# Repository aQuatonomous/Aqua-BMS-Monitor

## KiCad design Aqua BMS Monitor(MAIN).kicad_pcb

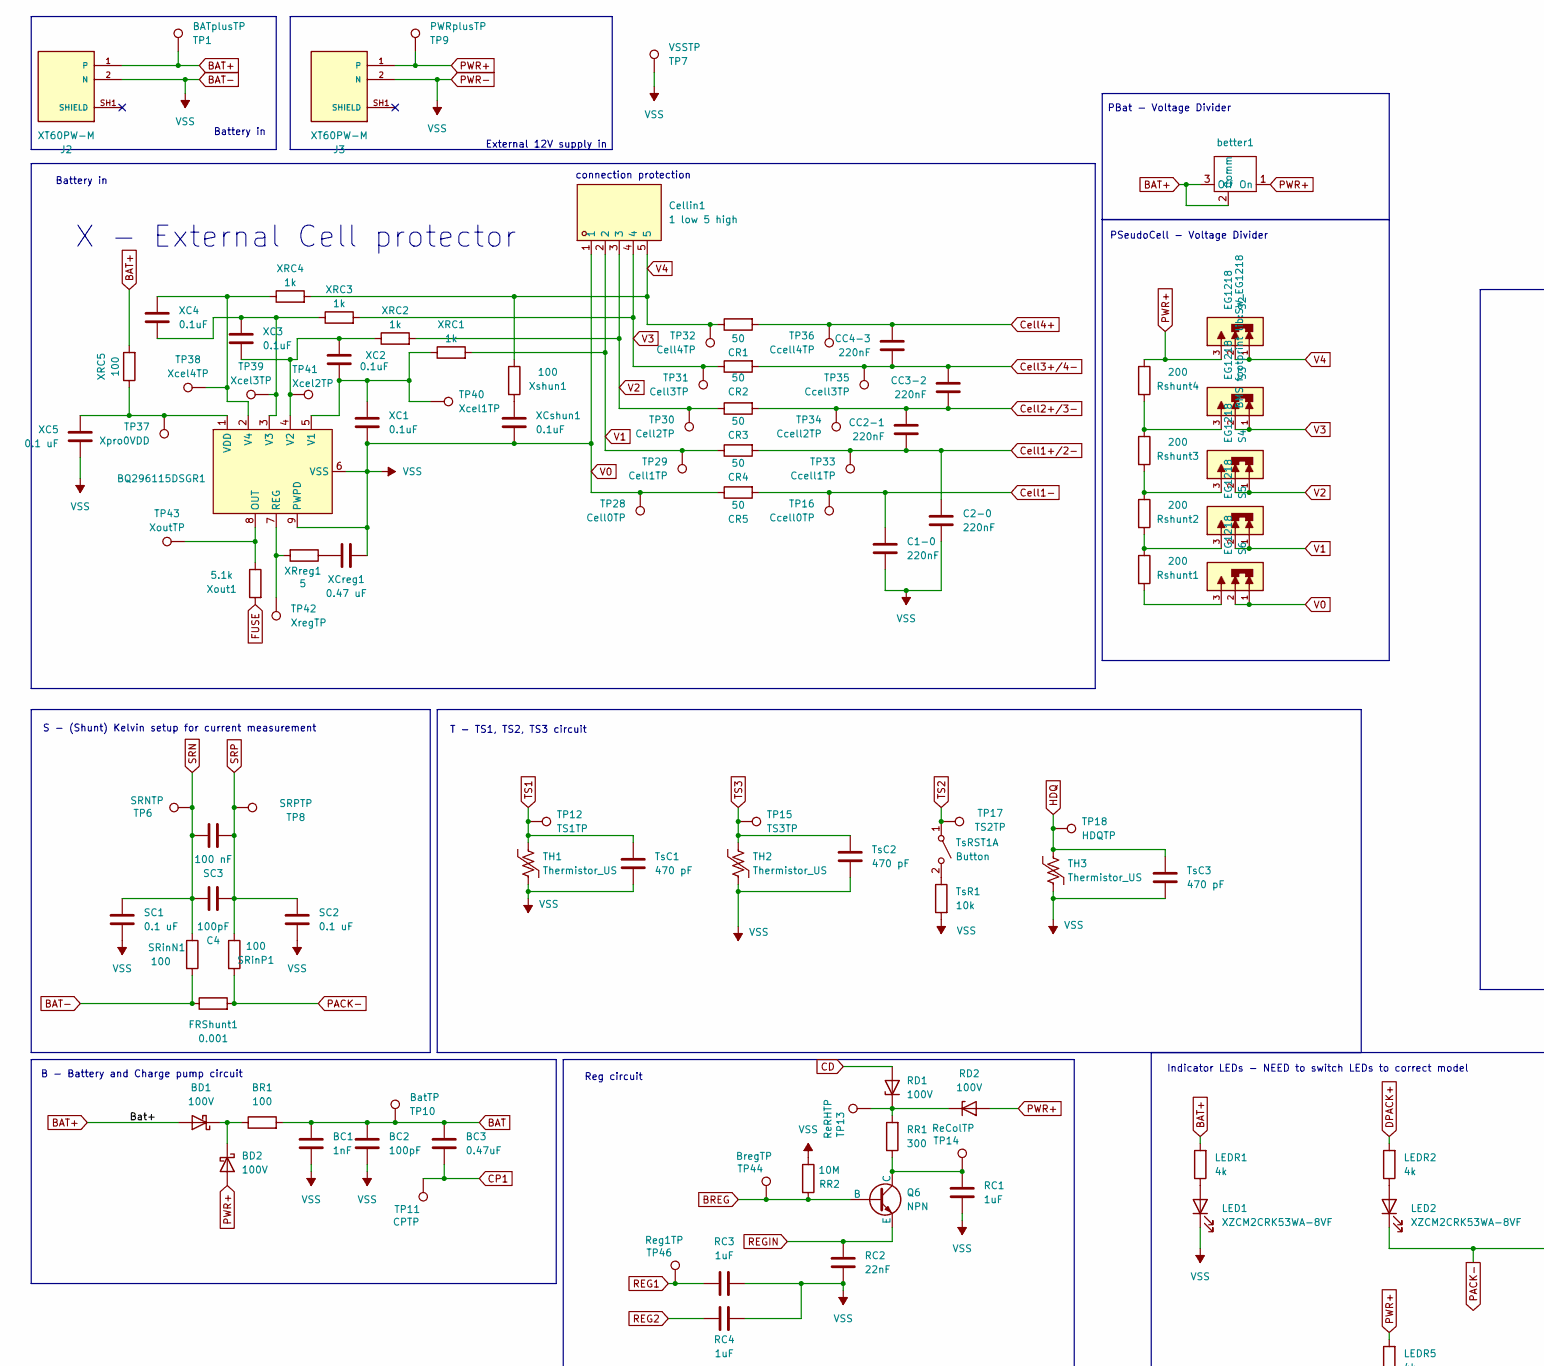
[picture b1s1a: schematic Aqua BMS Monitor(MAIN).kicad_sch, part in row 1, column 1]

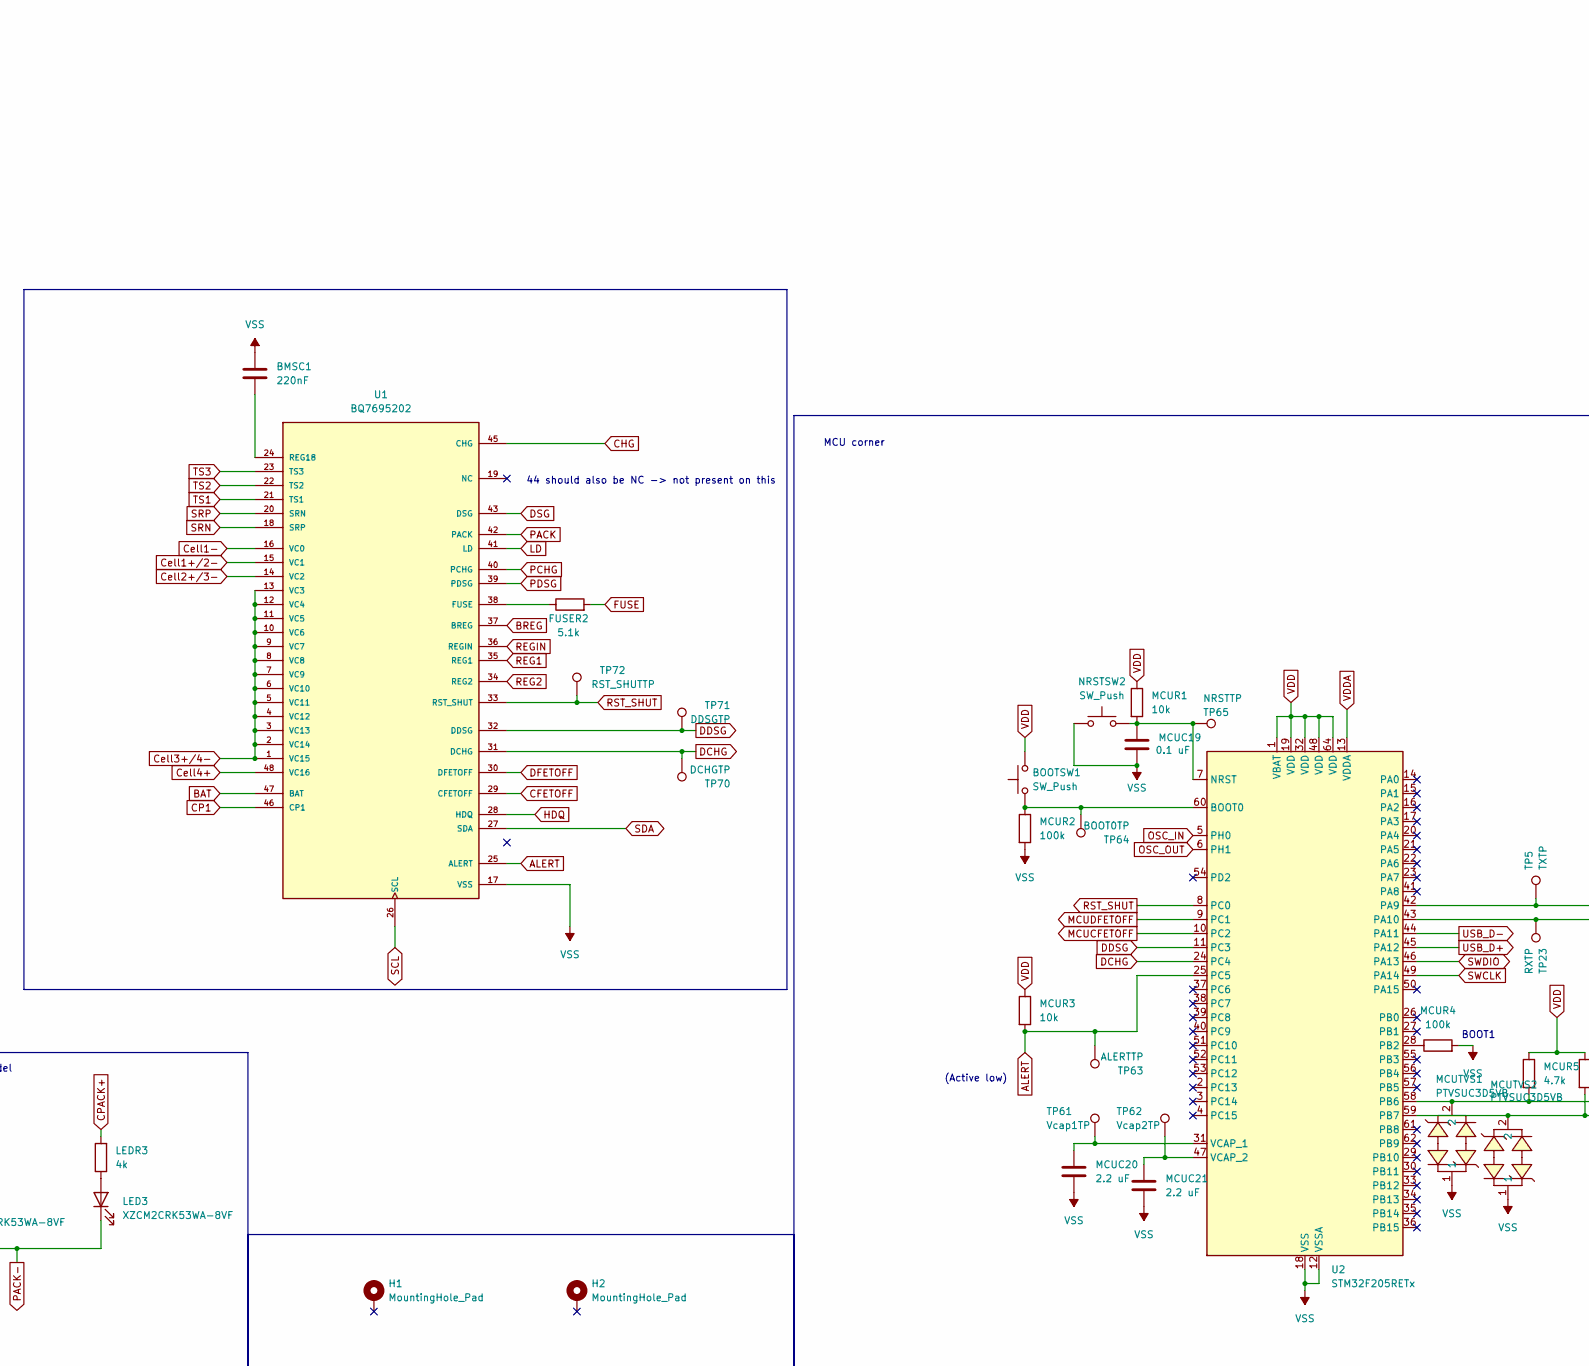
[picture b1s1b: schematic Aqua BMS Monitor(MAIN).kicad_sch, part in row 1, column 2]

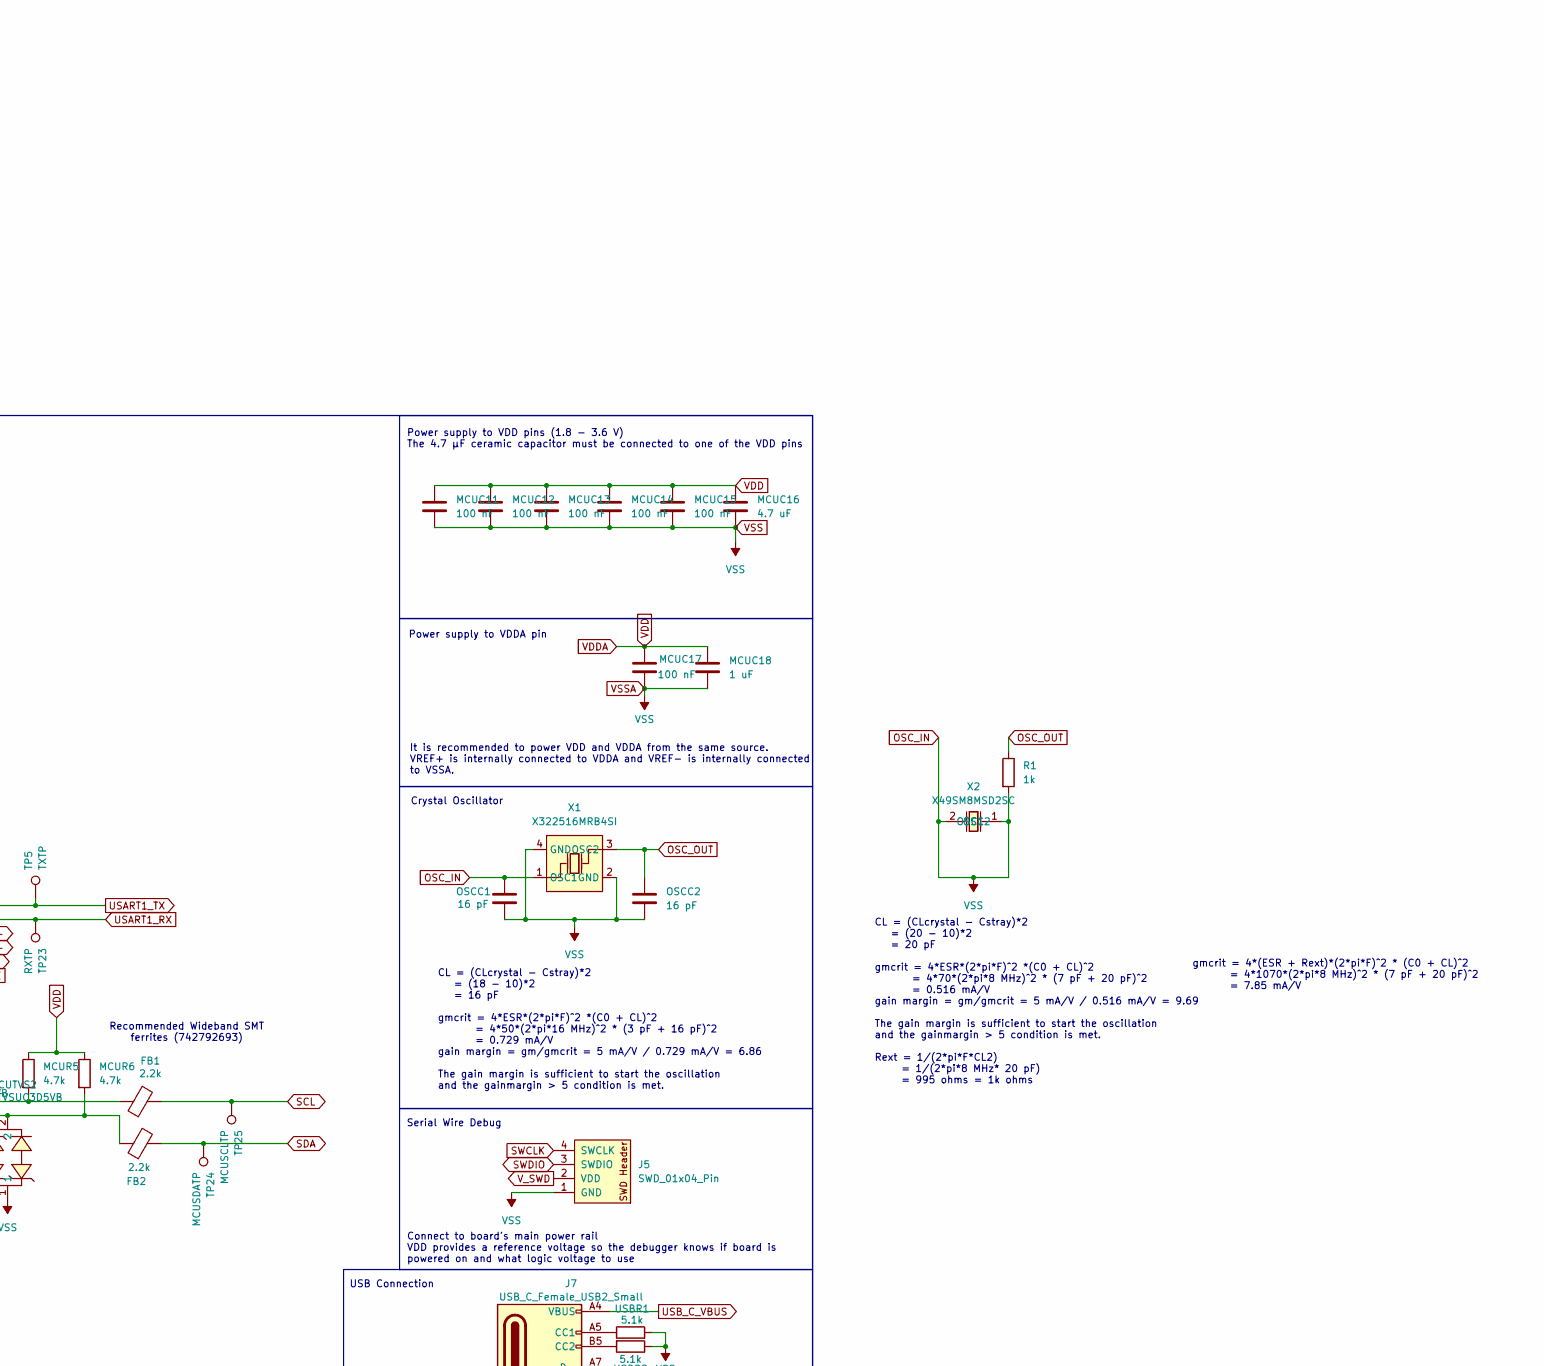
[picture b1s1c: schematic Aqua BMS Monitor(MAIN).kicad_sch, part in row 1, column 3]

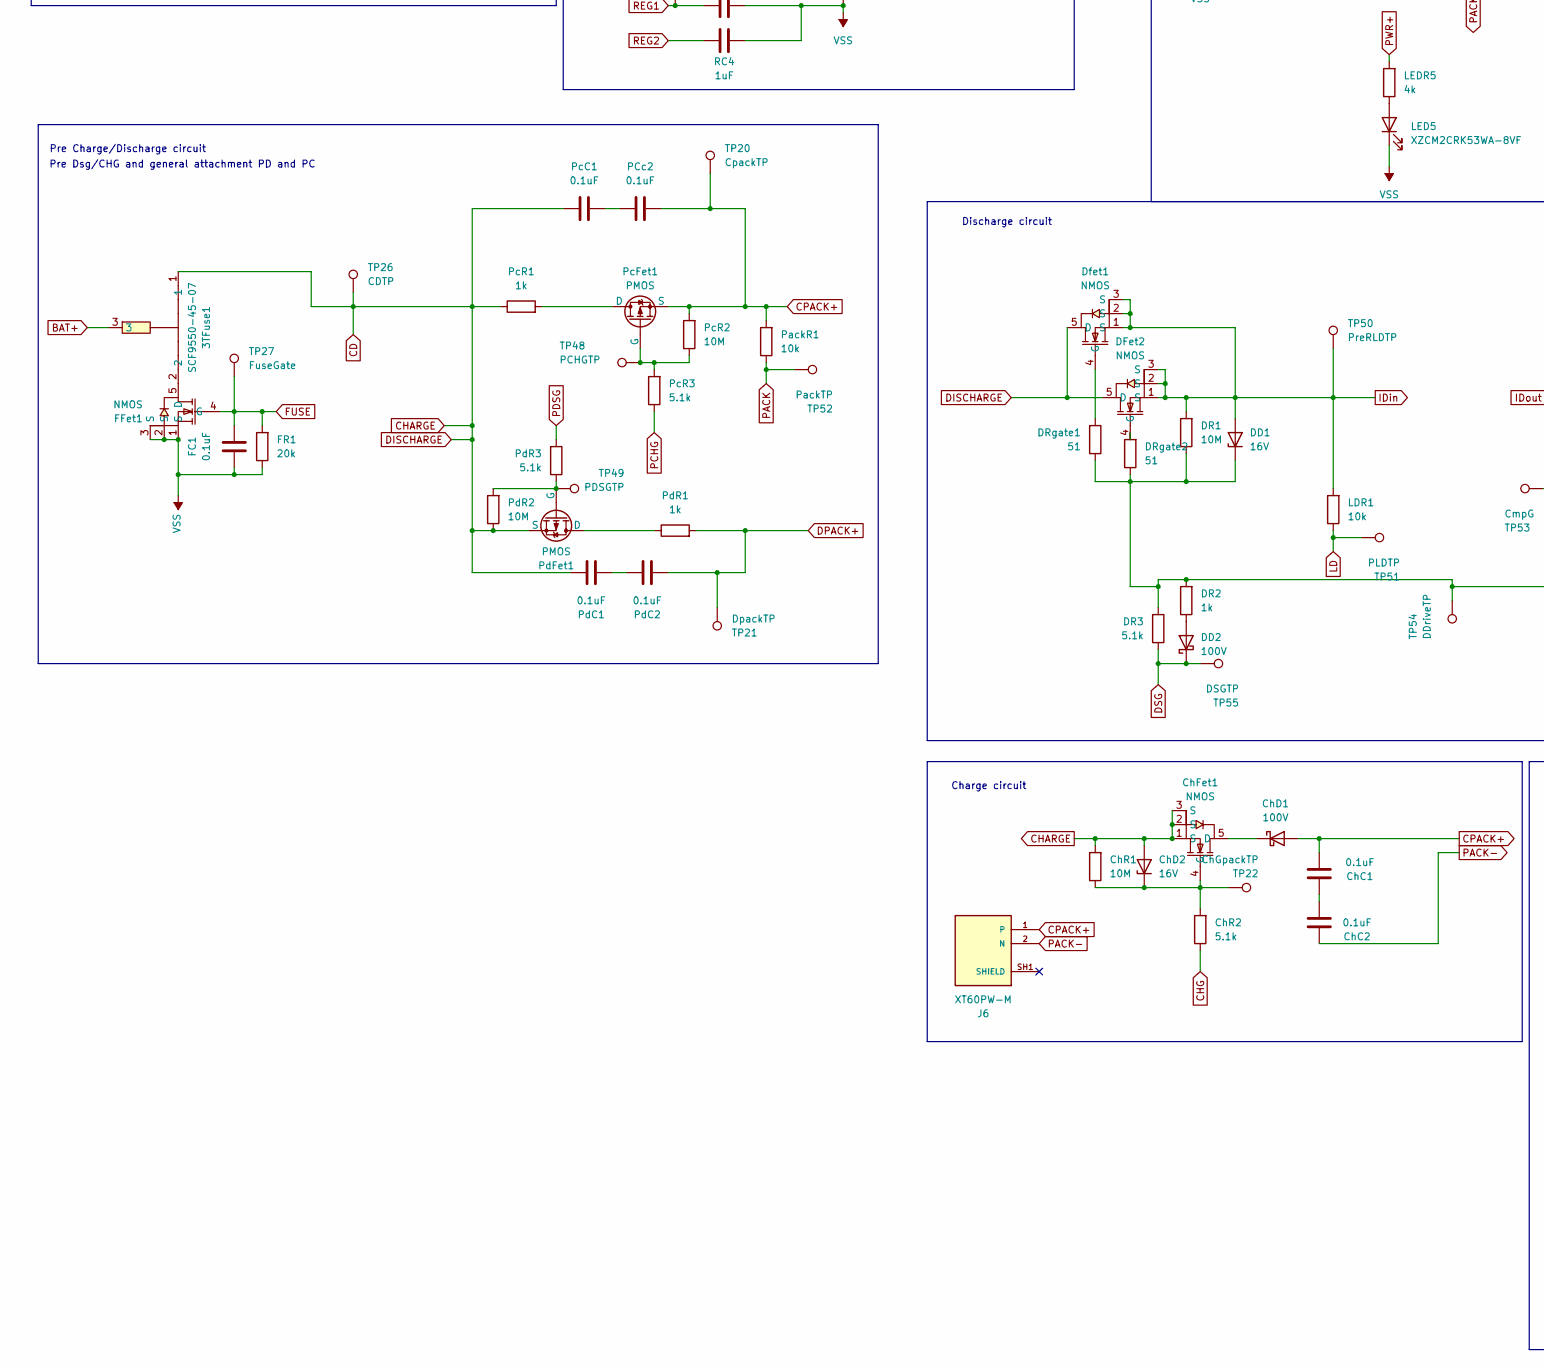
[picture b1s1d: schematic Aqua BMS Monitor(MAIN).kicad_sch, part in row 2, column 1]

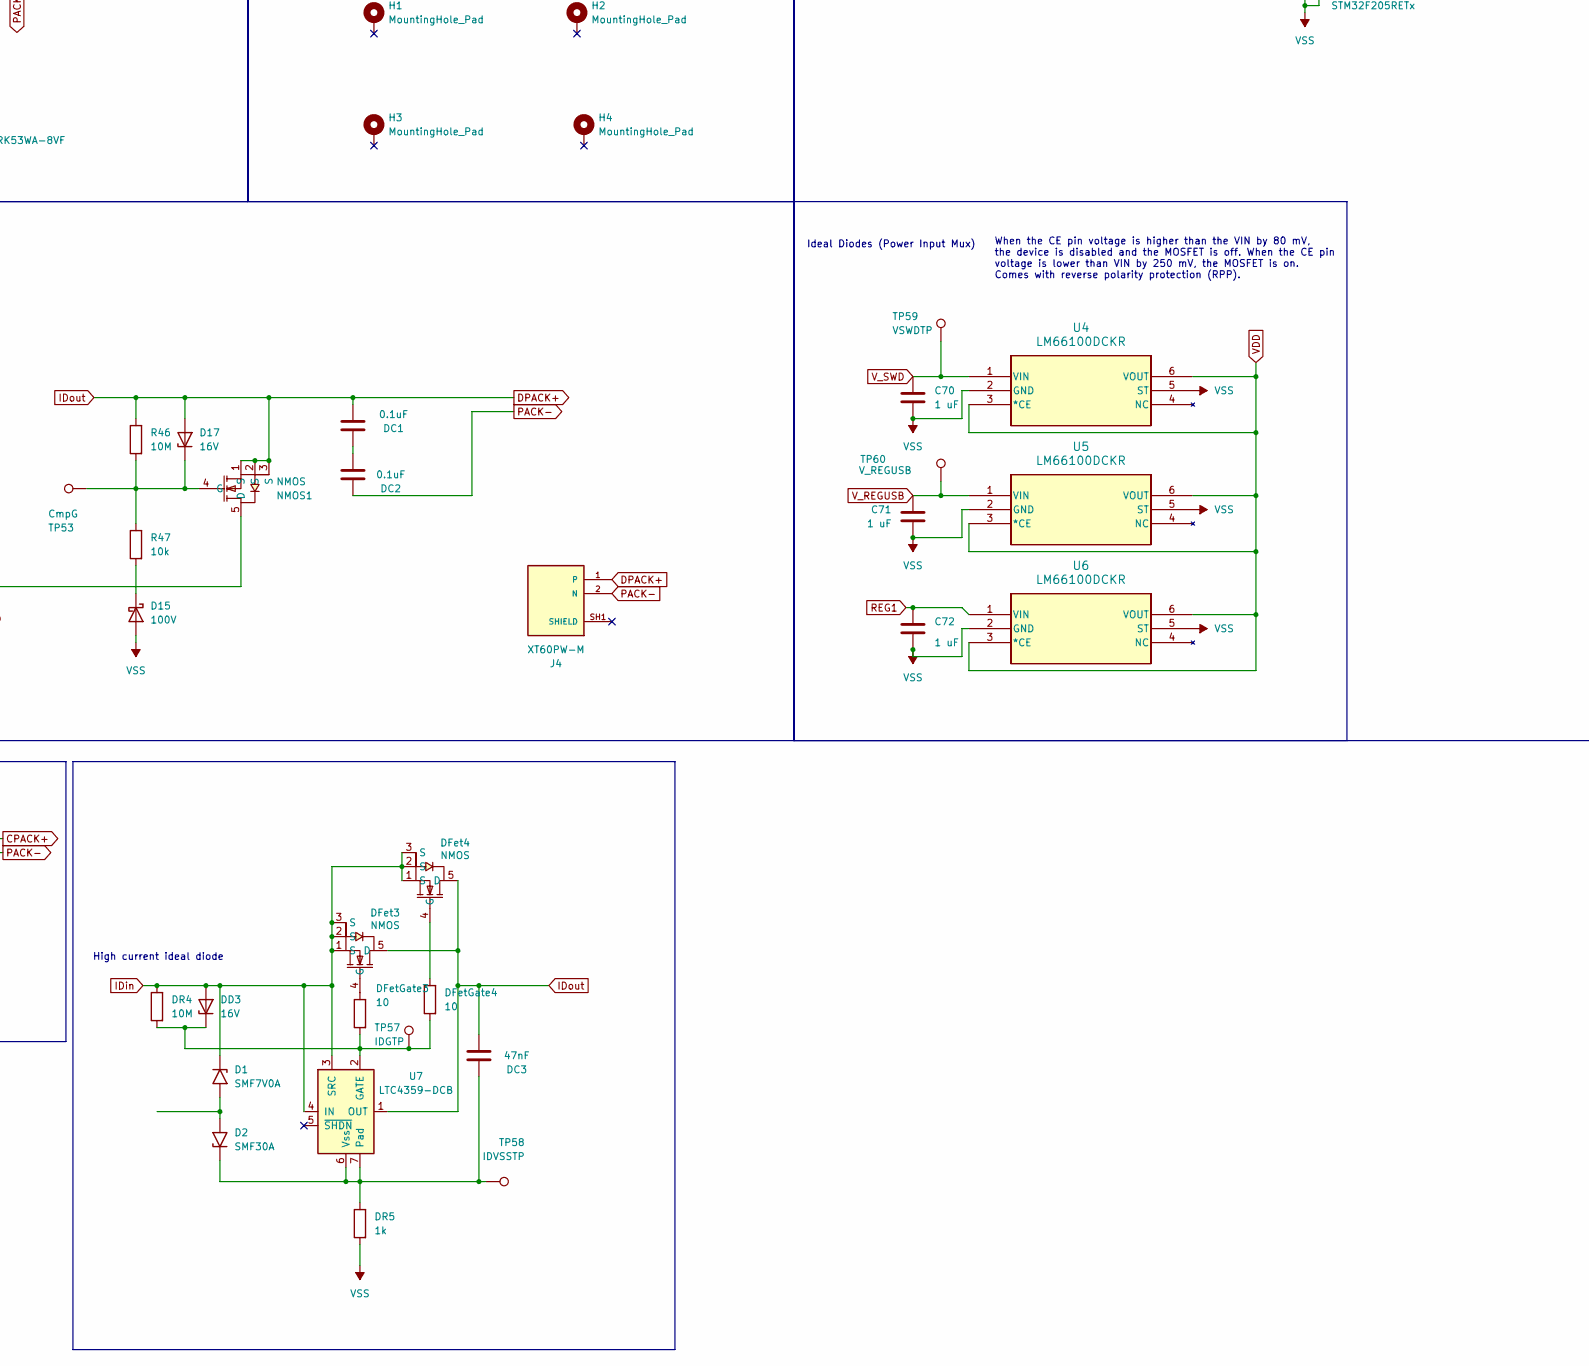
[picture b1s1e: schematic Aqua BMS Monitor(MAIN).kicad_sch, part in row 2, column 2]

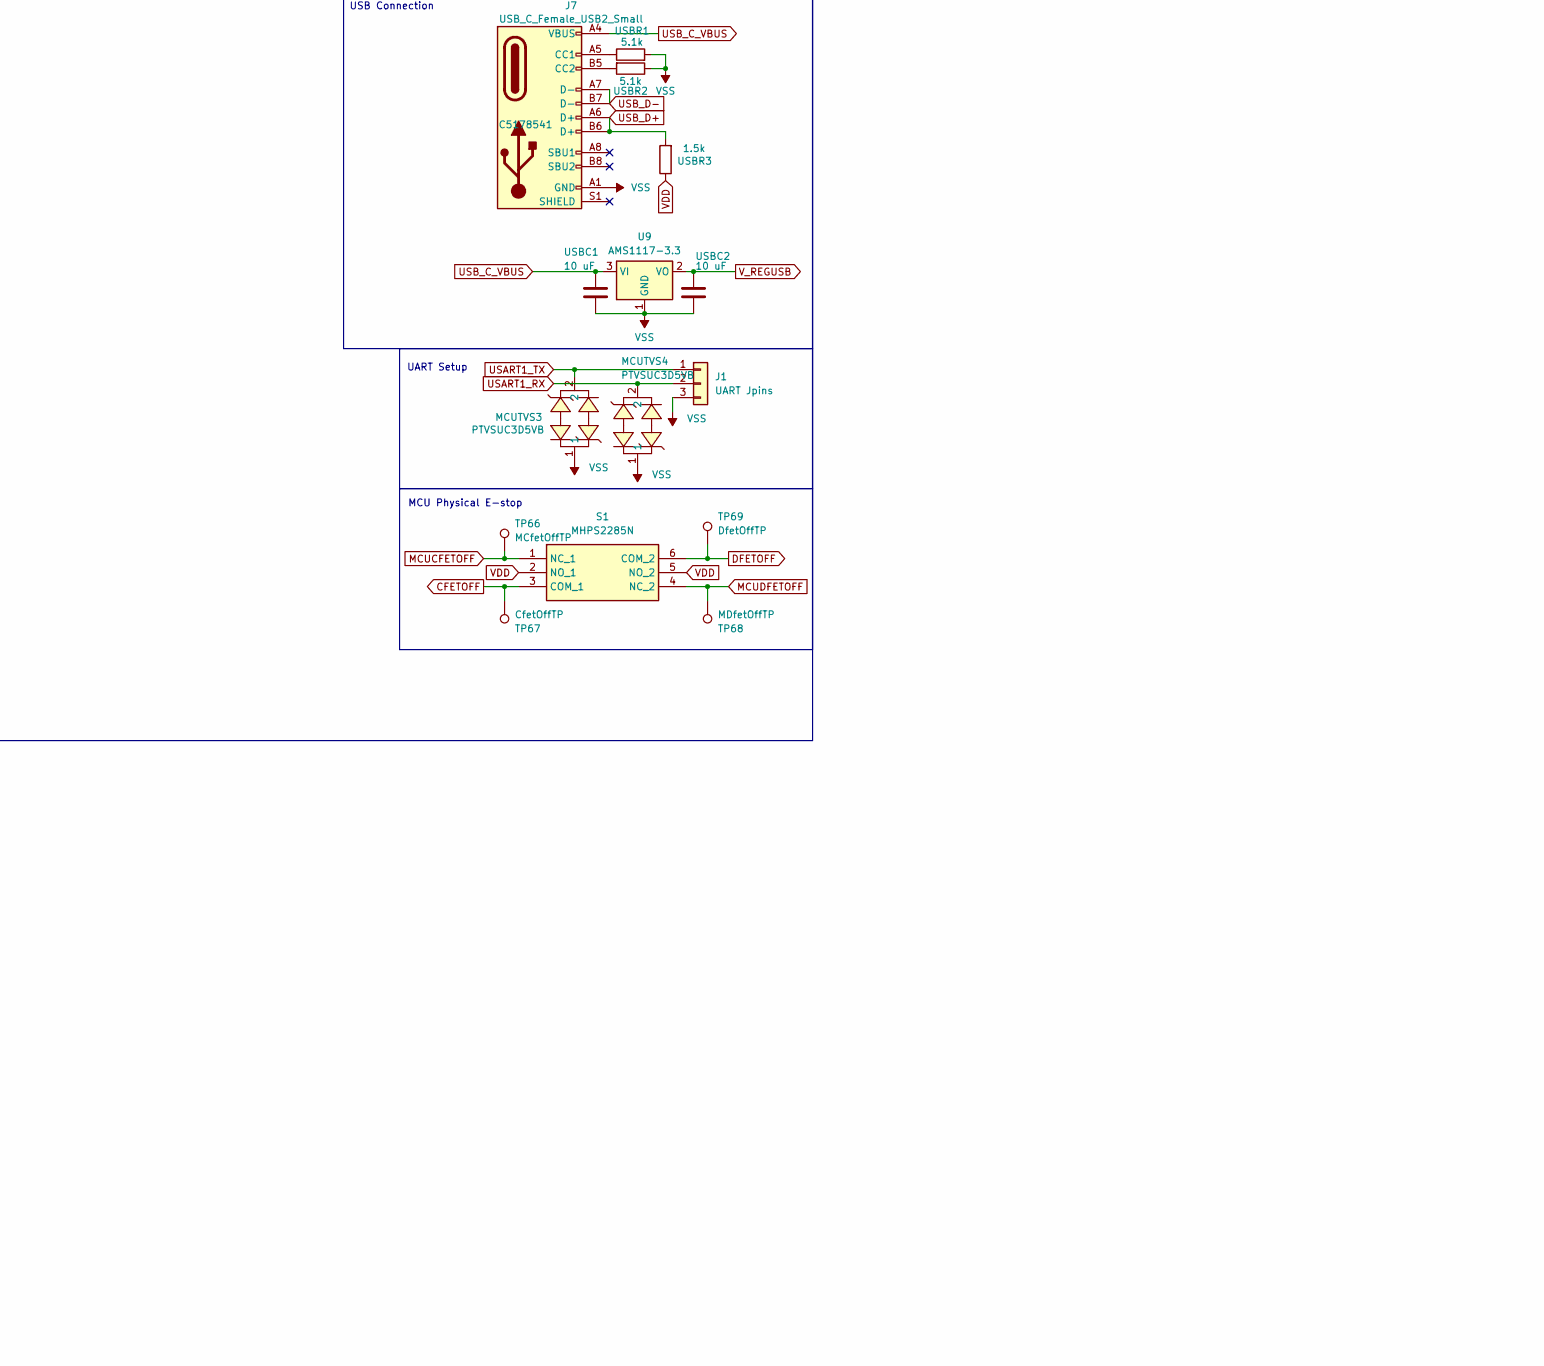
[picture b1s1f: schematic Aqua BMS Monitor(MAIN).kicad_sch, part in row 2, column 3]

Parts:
3TFuse1: SCF9550-45-07; FUSE-SMD_3P-L9.5-W5.0_SFK-5030X; MPN SCF9550-45-07; LCSC Part C3667292
BC1: 1nF; 1nF_C0805
BC2: 100pF; 100pF_C0603
BC3: 0.47uF; C_0603_1608Metric
BD1, BD2: 100V; 100V_Schottky
BMSC1: 220nF; C_0402_1005Metric
BOOTSW1: SW_Push; SW_Push_YZA-009
BQ296115DSGR1: BQ296115DSGR
BR1: 100; R_0603_1608Metric
C1-0, C2-0: 220nF; C_0402_1005Metric
C4: 100pF; 100pF_C0603
C70, C71, C72: 1 uF; 1uF_C0402
CC2-1, CC3-2, CC4-3: 220nF; C_0402_1005Metric
CR1, CR2, CR3, CR4, CR5: 50; 50_100mW_R0805
Cellin1: 1 low 5 high; CONN-TH_B5B-XH-A-LF-SN; MPN B5B-XH-A(LF)(SN); LCSC Part C157991
ChC1, ChC2: 0.1uF; C_0603_1608Metric
ChD1: 100V; 100V_Schottky
ChD2: 16V; 16V_Zener
ChFet1: NMOS; MPN H7534N; LCSC Part C49435644
ChR1: 10M; R_0603_1608Metric
ChR2: 5.1k; 5.1k_100mW_R0603
D1: SMF7V0A; D_SMF
D2: SMF30A; D_SMF
D15: 100V; 100V_Schottky
D17: 16V; 16V_Zener
DC1, DC2: 0.1uF; C_0603_1608Metric
DC3: 47nF; 47nF_C0603
DD1, DD3: 16V; 16V_Zener
DD2: 100V; 100V_Schottky
DFet2, DFet3, DFet4: NMOS; MPN H7534N; LCSC Part C49435644
DFetGate3, DFetGate4: 10; R_0603_1608Metric
DR1, DR4: 10M; R_0603_1608Metric
DR2: 1k; R_0603_1608Metric
DR3: 5.1k; 5.1k_100mW_R0603
DR5: 1k; 5.1k_R1210
DRgate1, DRgate2: 51; 51_R1206
Dfet1: NMOS; MPN H7534N; LCSC Part C49435644
FB1, FB2: 2.2k; 2.2k_Ferrite_Bead_L0603
FC1: 0.1uF; C_0603_1608Metric
FFet1: NMOS; MPN H7534N; LCSC Part C49435644
FR1: 20k; R_0603_1608Metric
FRShunt1: 0.001; 1m_Shunt_4W
FUSER2: 5.1k; 5.1k_100mW_R0603
H1, H2, H3, H4: MountingHole_Pad; MountingHole_3.2mm_M3_Pad_TopBottom
J1: UART Jpins; 3P_Pin_Header
J2, J3, J4, J6: XT60PW-M; AMASS_XT60PW-M; PARTREV 1.2
J5: SWD_01x04_Pin; HARWIN_M20-8890445; Digikey 952-3233-ND
J7: USB_C_Female_USB2_Small; USB_C_DB-108PWB; LCSC C5178541
LDR1: 10k; R_0603_1608Metric
LED1, LED2, LED3, LED5: XZCM2CRK53WA-8VF; LED0805-RD
LEDR1, LEDR2, LEDR3, LEDR5: 4k; 4k_R0805
MCUC11, MCUC12, MCUC13, MCUC14, MCUC15, MCUC17: 100 nF; 100nF_C0402
MCUC16: 4.7 uF; 4.7uF_C0402
MCUC18: 1 uF; 1uF_C0402
MCUC19: 0.1 uF; 100nF_C0402
MCUC20, MCUC21: 2.2 uF; 2.2uF_C0402
MCUR1, MCUR3: 10k; 10k_62.5mW_R0402
MCUR2, MCUR4: 100k; 100k_R0402
MCUR5, MCUR6: 4.7k; 4.7k_R0402
MCUTVS1, MCUTVS2, MCUTVS3, MCUTVS4: PTVSUC3D5VB; 5V_TVS_SOD-323_L1.8-W1.3-LS2.5-BI; MPN PTVSUC3D5VB; LCSC Part C918847
NMOS1: NMOS; MPN H7534N; LCSC Part C49435644
NRSTSW2: SW_Push; SW_Push_YZA-009
OSCC1, OSCC2: 16 pF; 16pF_C0402
PCc2: 0.1uF; C_0603_1608Metric
PackR1: 10k; 10k_R1206
PcC1: 0.1uF; C_0603_1608Metric
PcFet1: PMOS
PcR1: 1k; 1k_R1206
PcR2: 10M; R_0603_1608Metric
PcR3: 5.1k; 5.1k_100mW_R0603
PdC1, PdC2: 0.1uF; C_0603_1608Metric
PdFet1: PMOS
PdR1: 1k; R_0603_1608Metric
PdR2: 10M; R_0603_1608Metric
PdR3: 5.1k; 5.1k_100mW_R0603
Q6: NPN; NPN_BJT
R1: 1k
R46: 10M; R_0603_1608Metric
R47: 10k; R_0603_1608Metric
RC1, RC3, RC4: 1uF; 1uF_C0402
RC2: 22nF; C_0402_1005Metric
RD1, RD2: 100V; 100V_Schottky
RR1: 300; 300_250mW_R1206
RR2: 10M; R_0603_1608Metric
Rshunt1, Rshunt2, Rshunt3, Rshunt4: 200; 200_R1210
S1: MHPS2285N; Mouser Part Number 642-MHPS2285N
S2, S3, S4, S5, S6: EG1218; SW_EG1218
SC1, SC2: 0.1 uF; C_0402_1005Metric
SC3: 100 nF; C_0402_1005Metric
SRinN1: 100; R_0402_1005Metric
SRinP1: 100; R_0402_1005Metric
TH1, TH2, TH3: Thermistor_US; PTC_Thermistor_TMP6131LPGM
TP1: BATplusTP; TestPoint_Pad_D1.5mm
TP5: TXTP; TestPoint_Pad_D1.5mm
TP6: SRNTP; TestPoint_Pad_D1.0mm
TP7: VSSTP; TestPoint_Pad_1.5x1.5mm
TP8: SRPTP; TestPoint_Pad_D1.0mm
TP9: PWRplusTP; TestPoint_Pad_D1.5mm
TP10: BatTP; TestPoint_Pad_D1.0mm
TP11: CPTP; TestPoint_Pad_D1.0mm
TP12: TS1TP; TestPoint_Pad_D1.0mm
TP13: ReRHTP; TestPoint_Pad_D1.0mm
TP14: ReColTP; TestPoint_Pad_D1.0mm
TP15: TS3TP; TestPoint_Pad_D1.0mm
TP16: Ccell0TP; TestPoint_Pad_D1.0mm
TP17: TS2TP; TestPoint_Pad_D1.5mm
TP18: HDQTP; TestPoint_Pad_D1.0mm
TP20: CpackTP; TestPoint_Pad_D1.5mm
TP21: DpackTP; TestPoint_Pad_D1.5mm
TP22: ChGpackTP; TestPoint_Pad_D1.0mm
TP23: RXTP; TestPoint_Pad_D1.5mm
TP24: MCUSDATP; TestPoint_Pad_D1.5mm
TP25: MCUSCLTP; TestPoint_Pad_D1.5mm
TP26: CDTP; TestPoint_Pad_D1.5mm
TP27: FuseGate; TestPoint_Pad_D1.0mm
TP28: Cell0TP; TestPoint_Pad_D1.5mm
TP29: Cell1TP; TestPoint_Pad_D1.5mm
TP30: Cell2TP; TestPoint_Pad_D1.5mm
TP31: Cell3TP; TestPoint_Pad_D1.5mm
TP32: Cell4TP; TestPoint_Pad_D1.5mm
TP33: Ccell1TP; TestPoint_Pad_D1.0mm
TP34: Ccell2TP; TestPoint_Pad_D1.0mm
TP35: Ccell3TP; TestPoint_Pad_D1.0mm
TP36: Ccell4TP; TestPoint_Pad_D1.0mm
TP37: Xpro0VDD; TestPoint_Pad_D1.0mm
TP38: Xcel4TP; TestPoint_Pad_D1.0mm
TP39: Xcel3TP; TestPoint_Pad_D1.0mm
TP40: Xcel1TP; TestPoint_Pad_D1.0mm
TP41: Xcel2TP; TestPoint_Pad_D1.0mm
TP42: XregTP; TestPoint_Pad_D1.5mm
TP43: XoutTP; TestPoint_Pad_D1.0mm
TP44: BregTP; TestPoint_Pad_D1.0mm
TP46: Reg1TP; TestPoint_Pad_D1.0mm
TP48: PCHGTP; TestPoint_Pad_D1.0mm
TP49: PDSGTP; TestPoint_Pad_D1.0mm
TP50: PreRLDTP; TestPoint_Pad_D1.5mm
TP51: PLDTP; TestPoint_Pad_D1.0mm
TP52: PackTP; TestPoint_Pad_D1.5mm
TP53: CmpG; TestPoint_Pad_D1.0mm
TP54: DDriveTP; TestPoint_Pad_D1.0mm
TP55: DSGTP; TestPoint_Pad_D1.0mm
TP57: IDGTP; TestPoint_Pad_D1.0mm
TP58: IDVSSTP; TestPoint_Pad_D1.0mm
TP59: VSWDTP; TestPoint_Pad_D1.5mm
TP60: V_REGUSB; TestPoint_Pad_D1.5mm
TP61: Vcap1TP; TestPoint_Pad_D1.5mm
TP62: Vcap2TP; TestPoint_Pad_D1.5mm
TP63: ALERTTP; TestPoint_Pad_D1.5mm
TP64: BOOT0TP; TestPoint_Pad_D1.5mm
TP65: NRSTTP; TestPoint_Pad_D1.5mm
TP66: MCfetOffTP; TestPoint_Pad_D1.5mm
TP67: CfetOffTP; TestPoint_Pad_D1.5mm
TP68: MDfetOffTP; TestPoint_Pad_D1.5mm
TP69: DfetOffTP; TestPoint_Pad_D1.5mm
TP70: DCHGTP; TestPoint_Pad_D1.5mm
TP71: DDSGTP; TestPoint_Pad_D1.5mm
TP72: RST_SHUTTP; TestPoint_Pad_D1.5mm
TsC1, TsC2, TsC3: 470 pF; 470pF_C0402
TsR1: 10k; 10k_62.5mW_R0402
TsRST1: Button; SW_Push_YZA-009
U1: BQ7695202; BQ7695202PFBR; PARTREV B
U2: STM32F205RETx; LQFP-64_10x10mm_P0.5mm
U4, U5, U6: LM66100DCKR
U7: LTC4359-DCB; DFN-6-1EP_3x2mm_P0.5mm_EP1.65x1.35mm
U9: AMS1117-3.3; SOT-223-3_TabPin2
USBC1, USBC2: 10 uF; 10uF_C0603
USBR1, USBR2: 5.1k; 5.1k_100mW_R0603
USBR3: 1.5k; 1.5k_100mW_R0603
X1: X322516MRB4SI; 18pF_Oscillator_CRYSTAL-SMD_4P; MPN X322516MRB4SI; LCSC Part C70562
X2: X49SM8MSD2SC; CRYSTAL-SMD_L11.5-W4.8-LS12.7; MPN X49SM8MSD2SC; LCSC Part C12674
XC1, XC3, XC4: 0.1uF; C_0402_1005Metric
XC2: 0.1uF; C_0603_1608Metric
XC5: 0.1 uF; C_0402_1005Metric
XCreg1: 0.47 uF; 0.47 uF_C1210
XCshun1: 0.1uF; C_0603_1608Metric
XRC1, XRC2, XRC3, XRC4: 1k; 1k_R1206
XRC5: 100; R_0402_1005Metric
XRreg1: 5; 5_1W_R2512
Xout1: 5.1k; 5.1k_100mW_R0603
Xshun1: 100; R_0402_1005Metric
better1: 1101A2CQEA-Switch

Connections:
ALERT: MCUR3.2, TP63.1 (1_1), U1.25 (ALERT), U2.25 (PC5)
BAT: BC1.1, BC2.1, BC3.1, BR1.2, TP10.1 (1_1), U1.47 (BAT)
BAT+: 3TFuse1.3, BD1.2 (A), J2.1, LEDR1.2, TP1.1 (1_1), XRC5.2, better1.2 (Comm), better1.3 (Off)
BREG: Q6.2 (B), RR2.2, TP44.1 (1_1), U1.37 (BREG)
CD: 3TFuse1.1, ChD2.2 (A), ChFet1.1 (S), ChFet1.2 (S), ChFet1.3 (S), ChR1.2, DFet2.5 (D), Dfet1.5 (D), PcC1.1, PcR1.1, PdC1.1, PdFet1.3 (S), PdR2.1, RD1.2 (A), TP26.1 (1_1)
CFETOFF: S1.3 (COM_1), TP67.1 (1_1), U1.29 (CFETOFF)
CHG: ChR2.1, U1.45 (CHG)
CP1: BC3.2, TP11.1 (1_1), U1.46 (CP1)
CPACK+: ChC1.1, ChD1.2 (A), J6.1, LEDR3.2, PCc2.2, PackR1.2, PcFet1.3 (S), PcR2.2, TP20.1 (1_1)
Cell1+/2-: C2-0.1, CC2-1.1, CR4.2, TP33.1 (1_1), U1.15 (VC1)
Cell1-: C1-0.1, CR5.2, TP16.1 (1_1), U1.16 (VC0)
Cell2+/3-: CC2-1.2, CC3-2.1, CR3.2, TP34.1 (1_1), U1.14 (VC2)
Cell3+/4-: CC3-2.2, CC4-3.1, CR2.2, TP35.1 (1_1), U1.1 (VC15), U1.2 (VC14), U1.3 (VC13), U1.4 (VC12), U1.5 (VC11), U1.6 (VC10), U1.7 (VC9), U1.8 (VC8), U1.9 (VC7), U1.10 (VC6), U1.11 (VC5), U1.12 (VC4), U1.13 (VC3)
Cell4+: CC4-3.2, CR1.2, TP36.1 (1_1), U1.48 (VC16)
DCHG: TP70.1 (1_1), U1.31 (DCHG), U2.24 (PC4)
DDSG: TP71.1 (1_1), U1.32 (DDSG), U2.11 (PC3)
DFETOFF: S1.6 (COM_2), TP69.1 (1_1), U1.30 (DFETOFF)
DPACK+: D17.2 (A), DC1.1, DC3.1, DFet3.5 (D), DFet4.5 (D), J4.1, LEDR2.2, NMOS1.1 (S), NMOS1.2 (S), NMOS1.3 (S), PdC2.2, PdR1.2, R46.2, TP21.1 (1_1), U7.1 (OUT)
DSG: DD2.1 (K), DR3.1, TP55.1 (1_1), U1.43 (DSG)
FUSE: FC1.1, FFet1.4 (G), FR1.2, FUSER2.2, TP27.1 (1_1), Xout1.2
HDQ: TH3.1, TP18.1 (1_1), TsC3.1, U1.28 (HDQ)
IDin: D1.1 (A1), DD1.2 (A), DD3.2 (A), DFet2.1 (S), DFet2.2 (S), DFet2.3 (S), DFet3.1 (S), DFet3.2 (S), DFet3.3 (S), DFet4.1 (S), DFet4.2 (S), DFet4.3 (S), DR1.2, DR4.2, Dfet1.1 (S), Dfet1.2 (S), Dfet1.3 (S), LDR1.2, TP50.1 (1_1), U7.3 (SRC), U7.4 (IN)
LD: LDR1.1, TP51.1 (1_1), U1.41 (LD)
MCUCFETOFF: S1.1 (NC_1), TP66.1 (1_1), U2.10 (PC2)
MCUDFETOFF: S1.4 (NC_2), TP68.1 (1_1), U2.9 (PC1)
unnamed: BD1.1 (K), BD2.1 (K), BR1.1
unnamed: BQ296115DSGR1.8 (OUT), TP43.1 (1_1), Xout1.1
unnamed: BQ296115DSGR1.7 (REG), TP42.1 (1_1), XRreg1.2
unnamed: BQ296115DSGR1.5 (V1), TP40.1 (1_1), XC1.2, XC2.2, XRC1.1
unnamed: BQ296115DSGR1.4 (V2), TP41.1 (1_1), XC2.1, XC3.2, XRC2.1
unnamed: BQ296115DSGR1.3 (V3), TP39.1 (1_1), XC3.1, XC4.2, XRC3.1
unnamed: BQ296115DSGR1.2 (V4), TP38.1 (1_1), XC4.1, XRC4.1
unnamed: BQ296115DSGR1.1 (VDD), TP37.1 (1_1), XC5.1, XRC5.1
unnamed: ChC1.2, ChC2.1
unnamed: ChD1.1 (K), ChFet1.5 (D)
unnamed: ChD2.1 (K), ChFet1.4 (G), ChR1.1, ChR2.2, TP22.1 (1_1)
unnamed: D1.2 (A2), D2.2 (A2)
unnamed: D2.1 (A1), DC3.2, DR5.2, TP58.1 (1_1), U7.6 (Vss), U7.7 (Pad)
unnamed: D15.1 (K), R47.1
unnamed: D17.1 (K), NMOS1.4 (G), R46.1, R47.2, TP53.1 (1_1)
unnamed: DC1.2, DC2.1
unnamed: DD1.1 (K), DR1.1, DR2.2, DR3.2, DRgate1.1, DRgate2.1, NMOS1.5 (D), TP54.1 (1_1)
unnamed: DD2.2 (A), DR2.1
unnamed: DD3.1 (K), DFetGate3.1, DFetGate4.1, DR4.1, TP57.1 (1_1), U7.2 (GATE)
unnamed: DFet2.4 (G), DRgate2.2
unnamed: DFet3.4 (G), DFetGate3.2
unnamed: DFet4.4 (G), DFetGate4.2
unnamed: DRgate1.2, Dfet1.4 (G)
unnamed: 3TFuse1.2, FFet1.5 (D)
unnamed: J7.A5 (CC1), USBR1.1
unnamed: J7.B5 (CC2), USBR2.2
unnamed: LED1.2 (A), LEDR1.1
unnamed: LED2.2 (A), LEDR2.1
unnamed: LED3.2 (A), LEDR3.1
unnamed: LED5.2 (A), LEDR5.1
unnamed: PCc2.1, PcC1.2
unnamed: PcFet1.1 (D), PcR1.2
unnamed: PcFet1.2 (G), PcR2.1, PcR3.2, TP48.1 (1_1)
unnamed: PdC1.2, PdC2.1
unnamed: PdFet1.1 (D), PdR1.1
unnamed: PdFet1.2 (G), PdR2.2, PdR3.1, TP49.1 (1_1)
unnamed: Q6.1 (C), RC1.1, RR1.1, TP14.1 (1_1)
unnamed: RD1.1 (K), RD2.1 (K), RR1.2, TP13.1 (1_1)
unnamed: Rshunt1.1, Rshunt2.2, S5.3
unnamed: Rshunt1.2, S6.3
unnamed: Rshunt2.1, Rshunt3.2, S4.3
unnamed: Rshunt3.1, Rshunt4.2, S3.3
unnamed: TsR1.1, TsRST1.2 (B)
unnamed: FUSER2.1, U1.38 (FUSE)
unnamed: BMSC1.2, U1.24 (REG18)
unnamed: BOOTSW1.1, MCUR2.1, TP64.1 (1_1), U2.60 (BOOT0)
unnamed: MCUC19.1, MCUR1.2, NRSTSW2.2, TP65.1 (1_1), U2.7 (NRST)
unnamed: MCUR4.1, U2.28 (PB2)
unnamed: FB1.1, MCUR5.2, MCUTVS1.2, U2.58 (PB6)
unnamed: FB2.1, MCUR6.2, MCUTVS2.2, U2.59 (PB7)
unnamed: MCUC20.1, TP61.1 (1_1), U2.31 (VCAP_1)
unnamed: MCUC21.1, TP62.1 (1_1), U2.47 (VCAP_2)
unnamed: XCreg1.1, XRreg1.1
unnamed: XCshun1.1, Xshun1.2
OSC_OUT: OSCC2.1, R1.1, U2.6 (PH1), X1.3 (OSC2)
PACK: PackR1.1, TP52.1 (1_1), U1.42 (PACK)
PACK-: ChC2.2, DC2.2, FRShunt1.2, J4.2 (N), J6.2 (N), LED2.1 (K), LED3.1 (K), SRinP1.2
PCHG: PcR3.1, U1.40 (PCHG)
PDSG: PdR3.2, U1.39 (PDSG)
PWR+: BD2.2 (A), J3.1, LEDR5.2, RD2.2 (A), Rshunt4.1, S2.3, TP9.1 (1_1), better1.1 (On)
REG1: C72.1, RC3.2, TP46.1 (1_1), U1.35 (REG1), U6.1 (VIN)
REG2: RC4.2, U1.34 (REG2)
REGIN: Q6.3 (E), RC2.1, U1.36 (REGIN)
RST_SHUT: TP72.1 (1_1), U1.33 (RST_SHUT), U2.8 (PC0)
SCL: FB1.2, TP25.1 (1_1), U1.26 (SCL)
SDA: FB2.2, TP24.1 (1_1), U1.27 (SDA)
SRN: C4.1, SC1.1, SC3.1, SRinN1.1, TP6.1 (1_1), U1.18 (SRP)
SRP: C4.2, SC2.1, SC3.2, SRinP1.1, TP8.1 (1_1), U1.20 (SRN)
SWCLK: J5.4 (SWCLK), U2.49 (PA14)
SWDIO: J5.3 (SWDIO), U2.46 (PA13)
TS1: TH1.1, TP12.1 (1_1), TsC1.1, U1.21 (TS1)
TS2: TP17.1 (1_1), TsRST1.1 (A), U1.22 (TS2)
TS3: TH2.1, TP15.1 (1_1), TsC2.1, U1.23 (TS3)
USART1_RX: J1.2, MCUTVS4.2, TP23.1 (1_1), U2.43 (PA10)
USART1_TX: J1.1, MCUTVS3.2, TP5.1 (1_1), U2.42 (PA9)
USB_C_VBUS: J7.A4 (VBUS), J7.A9 (VBUS), J7.B4 (VBUS), J7.B9 (VBUS), U9.3 (VI), USBC1.1
USB_D+: J7.A6 (D+), J7.B6 (D+), U2.45 (PA12), USBR3.2
USB_D-: J7.A7 (D-), J7.B7 (D-), U2.44 (PA11)
V1: CR4.1, Cellin1.2, S5.1, S5.2, TP29.1 (1_1), XRC1.2
V2: CR3.1, Cellin1.3, S4.1, S4.2, TP30.1 (1_1), XRC2.2
V3: CR2.1, Cellin1.4, S3.1, S3.2, TP31.1 (1_1), XRC3.2
V4: CR1.1, Cellin1.5, S2.1, S2.2, TP32.1 (1_1), XRC4.2, Xshun1.1
VDD: BOOTSW1.2, MCUC11.1, MCUC12.1, MCUC13.1, MCUC14.1, MCUC15.1, MCUC16.1, MCUC17.1, MCUC18.1, MCUR1.1, MCUR3.1, MCUR5.1, MCUR6.1, S1.2 (NO_1), S1.5 (NO_2), U2.1 (VBAT), U2.13 (VDDA), U2.19 (VDD), U2.32 (VDD), U2.48 (VDD), U2.64 (VDD), U4.3 (*CE), U4.6 (VOUT), U5.3 (*CE), U5.6 (VOUT), U6.3 (*CE), U6.6 (VOUT), USBR3.1
V_REGUSB: C71.1, TP60.1 (1_1), U5.1 (VIN), U9.2 (VO), USBC2.1
V_SWD: C70.1, J5.2 (VDD), TP59.1 (1_1), U4.1 (VIN)

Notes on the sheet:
Ideal Diodes (Power Input Mux)
Power supply to VDD pins (1.8 - 3.6 V) The 4.7 µF ceramic capacitor must be connected to one of the VDD pins
High current ideal diode
Pre Charge/Discharge circuit
When the CE pin voltage is higher than the VIN by 80 mV, the device is disabled and the MOSFET is off. When the CE pin voltage is lower than VIN by 250 mV, the MOSFET is on. Comes with reverse polarity protection (RPP).
44 should also be NC -> not present on this
S - (Shunt) Kelvin setup for current measurement
B - Battery and Charge pump circuit
Reg circuit
X - External Cell protector
UART Setup
(Active low)
Power supply to VDDA pin
Battery in
MCU Physical E-stop
PBat - Voltage Divider
gmcrit = 4*(ESR + Rext)*(2*pi*F)^2 * (C0 + CL)^2 = 4*1070*(2*pi*8 MHz)^2 * (7 pF + 20 pF)^2 = 7.85 mA/V
CL = (CLcrystal - Cstray)*2 = (18 - 10)*2 = 16 pF gmcrit = 4*ESR*(2*pi*F)^2 *(C0 + CL)^2 = 4*50*(2*pi*16 MHz)^2 * (3 pF + 16 pF)^2 = 0.729 mA/V gain margin = gm/gmcrit = 5 mA/V / 0.729 mA/V = 6.86 The gain margin is sufficient to start the oscillation and the gainmargin > 5 condition is met.
MCU corner
Discharge circuit
USB Connection
Connect to board's main power rail VDD provides a reference voltage so the debugger knows if board is powered on and what logic voltage to use
Pre Dsg/CHG and general attachment PD and PC
PSeudoCell - Voltage Divider
Crystal Oscillator
T - TS1, TS2, TS3 circuit
connection protection
BOOT1
Recommended Wideband SMT ferrites (742792693)
External 12V supply in
CL = (CLcrystal - Cstray)*2 = (20 - 10)*2 = 20 pF gmcrit = 4*ESR*(2*pi*F)^2 *(C0 + CL)^2 = 4*70*(2*pi*8 MHz)^2 * (7 pF + 20 pF)^2 = 0.516 mA/V gain margin = gm/gmcrit = 5 mA/V / 0.516 mA/V = 9.69 The gain margin is sufficient to start the oscillation and the gainmargin > 5 condition is met. Rext = 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
Serial Wire Debug
Charge circuit
Indicator LEDs - NEED to switch LEDs to correct model
It is recommended to power VDD and VDDA from the same source. VREF+ is internally connected to VDDA and VREF- is internally connected to VSSA.

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
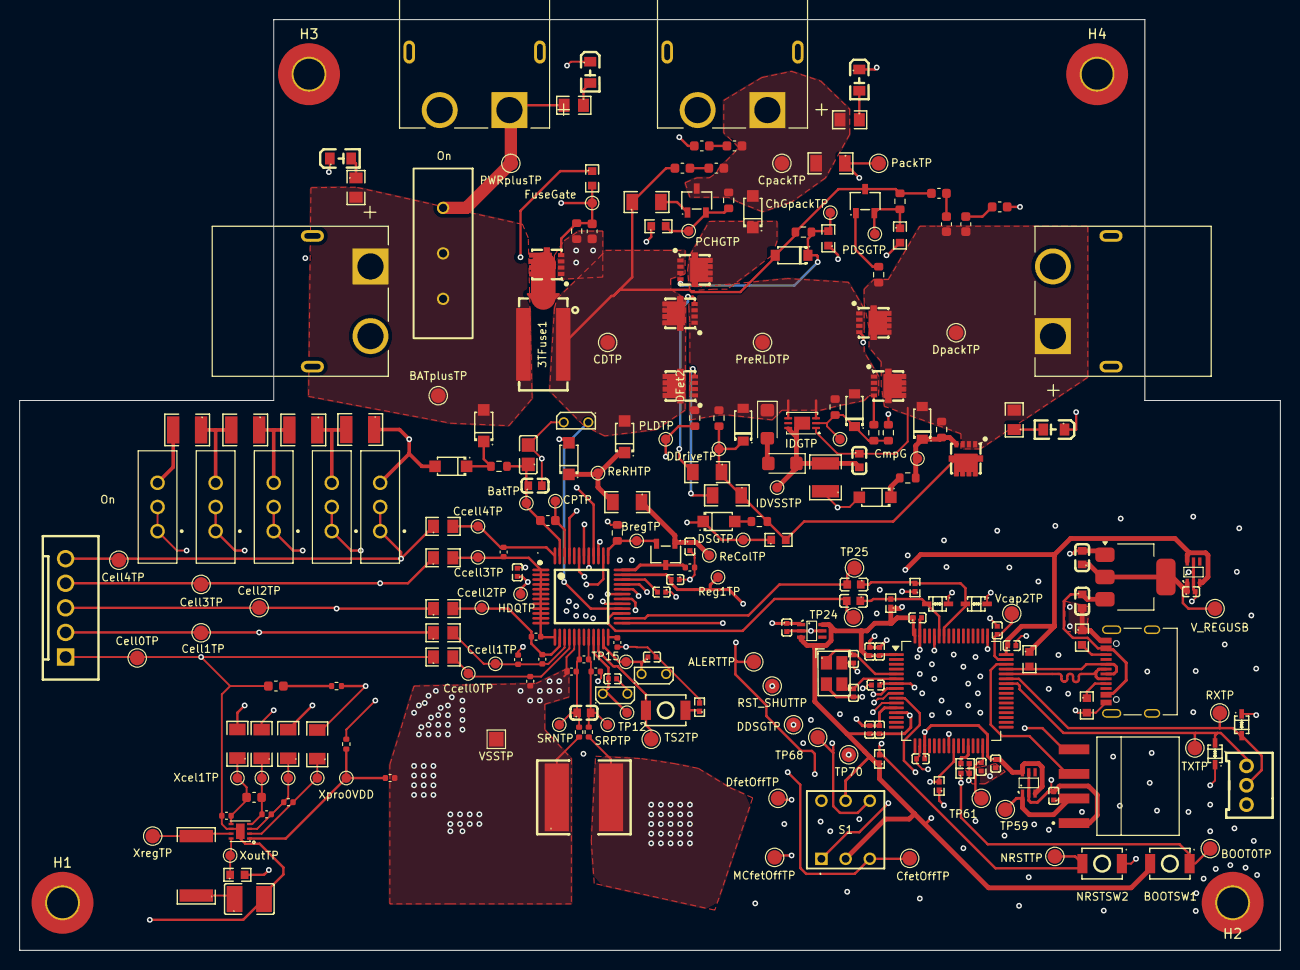
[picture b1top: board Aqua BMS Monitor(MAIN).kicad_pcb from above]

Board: 4 copper layers, 130.2 x 96.2 mm, 248 parts (0 on the bottom side), 112 nets.

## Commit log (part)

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2026-03-31 Initial setup and some organization
2026-03-31 setup
2026-03-31 Updates
    Cell monitor and shunt resistor complete
2026-03-31 Updates
    Thermosister and BAT/CP1 circuit updated
2026-03-31 Main circuits done
    All circuits I (kinda) understand are organised
2026-04-01 Commits before fork
2026-05-12 Big Updates
2026-05-24 V1 Parellel paths
2026-05-31 Discharge/Charge Circuit v1 done
    Up for review and explanation
2026-06-04 STM32 Connections
    First version, definitely needs some changes
2026-06-04 aQua BMS MCU Updated June 4
    Fixed? VCAP1 and VCAP2 connections, added BOOT0 pin connection
2026-06-04 changed size
2026-06-10 Aqua BMS Monitor and MCU
    Added STM32 schematic to main sheet, fixed some pins on MCU
2026-06-15 Updated June 15
    Changes to 2nd-level battery overvoltage protection circuit
2026-06-17 Updated June 17
2026-06-19 Updated June 19
